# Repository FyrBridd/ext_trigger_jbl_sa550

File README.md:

# WiiM trigger to JBL SA550 serial dongle

A small inline board, powered by a WiiM Ultra's 12 V trigger output, that keeps
a JBL SA550 Classic amplifier switched on and on its STB input over RS232.

**Status (2026-11-11):** board designed and checked, firmware written and
tested against a simulated amp, enclosure designed and checked against the
board and cables. Nothing has been ordered, printed or run on hardware.

## Where to look

| To | Read |
|---|---|
| Review the board before ordering | `docs/hardware-review.md` |
| See the schematic and board | `hardware/fab/schematic.pdf`, `hardware/fab/board.pdf` |
| Check the sums | `docs/hardware-calculations.md` |
| Order from JLCPCB | `docs/hardware-review.md`, section 6 |
| Buy the two cables | `docs/cables.md` |
| Review, order and assemble the enclosure | `docs/enclosure.md`, `enclosure/out/enclosure.pdf` |
| Flash the chip | `docs/flashing.md` |
| Get the first board working | `docs/bring-up.md` |
| Understand the amp's protocol | `docs/research.md` |
| Understand the design decisions | `docs/superpowers/specs/2026-11-10-wiim-trigger-jbl-dongle-design.md` |

## Working on it

All tools (KiCad 10, the AVR compiler, CadQuery, the tests) run in a Docker container.
Run everything through the wrapper `tools/dev`, or use the make targets:

| Command | Does |
|---|---|
| `make hw` | Regenerates the schematic, board and JLCPCB files from `hardware/design/` |
| `make hw-test` | Checks them: KiCad rule checks, schematic against board, files against the circuit |
| `make stock` | Checks every part is in stock at JLCPCB |
| `make fw-test` | Runs the firmware's tests on this machine, against a simulated amp |
| `make fw` | Builds the 16 firmware files in `firmware/release/` |
| `make route` | Re-runs the board autorouter (only after changing the circuit or placement) |
| `make enc` | Regenerates the enclosure's STEP and STL files, pictures and drawing in `enclosure/out/` |
| `make enc-test` | Checks the enclosure fits the board, cables and screws |

The circuit lives in `hardware/design/circuit.py`, the board placement in
`hardware/design/layout.py`, the firmware in `firmware/src/`, the enclosure
in `enclosure/params.py` and `enclosure/model.py`. Files under
`hardware/dongle/`, `hardware/fab/` and `enclosure/out/` are generated; do
not edit them.

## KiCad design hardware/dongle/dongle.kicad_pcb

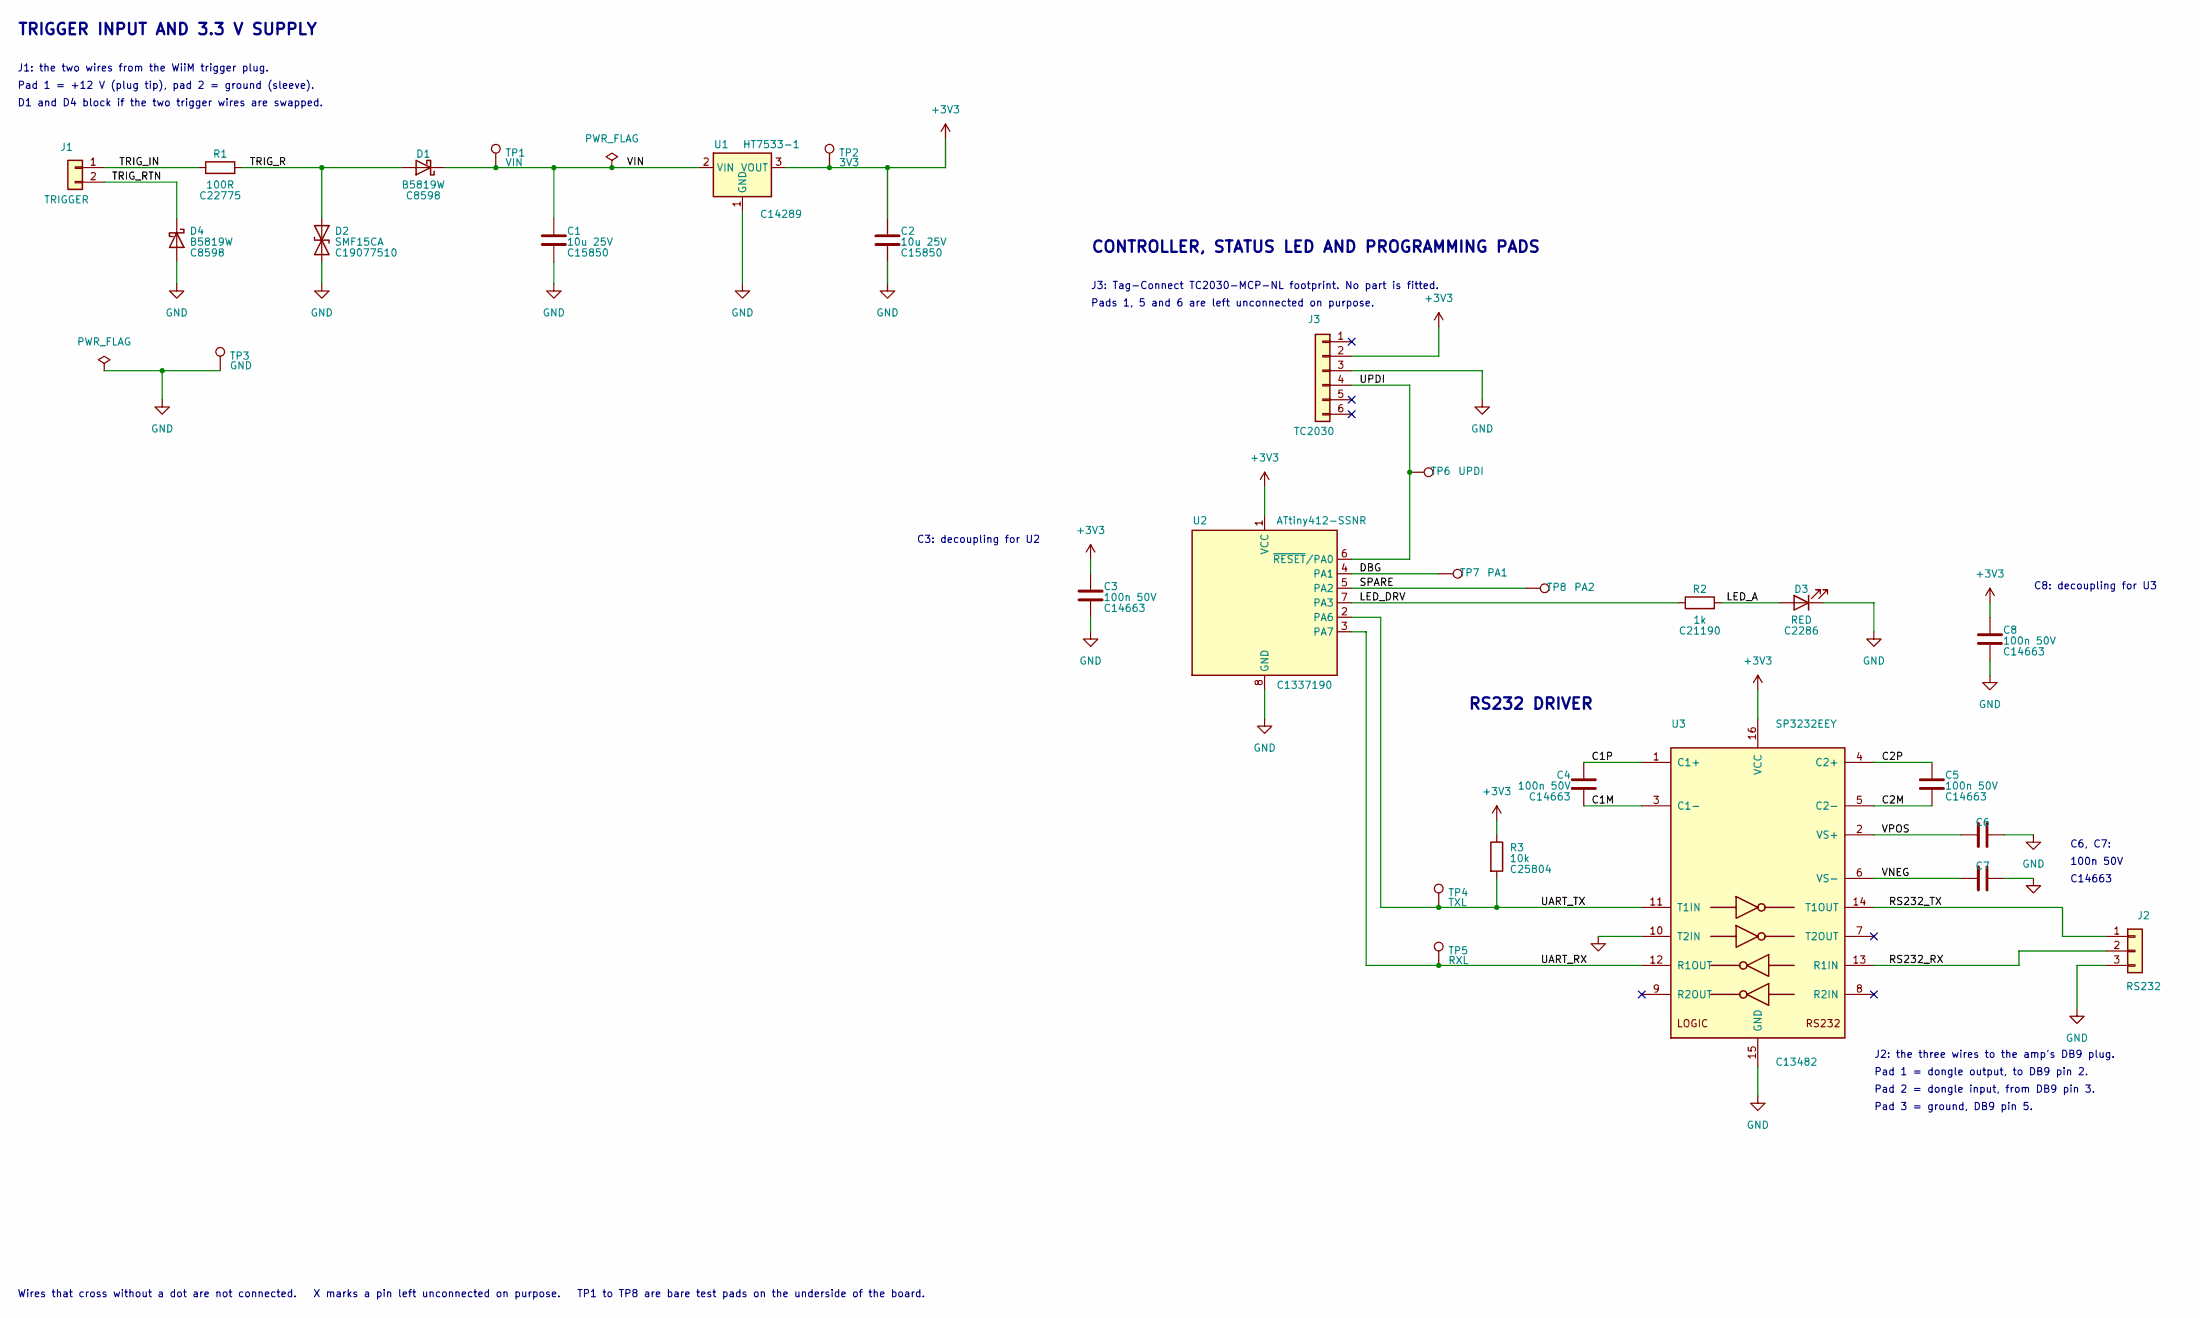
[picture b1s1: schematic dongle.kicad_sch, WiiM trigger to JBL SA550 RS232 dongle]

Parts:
C1, C2: 10u 25V; C_0805_2012Metric; LCSC C15850
C3, C4, C5, C6, C7, C8: 100n 50V; C_0603_1608Metric; LCSC C14663
D1, D4: B5819W; D_SOD-123; LCSC C8598
D2: SMF15CA; D_SOD-123F; LCSC C19077510
D3: RED; LED_0603_1608Metric; LCSC C2286
J1: TRIGGER; WirePads_1x02_Strain
J2: RS232; WirePads_1x03_Strain
J3: TC2030; TC2030-MCP-NL
R1: 100R; R_0603_1608Metric; LCSC C22775
R2: 1k; R_0603_1608Metric; LCSC C21190
R3: 10k; R_0603_1608Metric; LCSC C25804
TP1: VIN; TestPoint_Pad_D1.0mm
TP2: 3V3; TestPoint_Pad_D1.0mm
TP3: GND; TestPoint_Pad_D1.0mm
TP4: TXL; TestPoint_Pad_D1.0mm
TP5: RXL; TestPoint_Pad_D1.0mm
TP6: UPDI; TestPoint_Pad_D1.0mm
TP7: PA1; TestPoint_Pad_D1.0mm
TP8: PA2; TestPoint_Pad_D1.0mm
U1: HT7533-1; SOT-89-3; LCSC C14289
U2: ATtiny412-SSNR; SOIC-8_3.9x4.9mm_P1.27mm; LCSC C1337190
U3: SP3232EEY; TSSOP-16_4.4x5mm_P0.65mm; LCSC C13482

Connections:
+3V3: C2.1, C3.1, C8.1, J3.2, R3.1, TP2.1, U1.3 (VOUT), U2.1 (VCC), U3.16 (VCC)
/C1M: C4.2, U3.3 (C1-)
/C1P: C4.1, U3.1 (C1+)
/C2M: C5.2, U3.5 (C2-)
/C2P: C5.1, U3.4 (C2+)
/DBG: TP7.1, U2.4 (PA1)
/LED_A: D3.2 (A), R2.2
/LED_DRV: R2.1, U2.7 (PA3)
/RS232_RX: J2.2, U3.13 (R1IN)
/RS232_TX: J2.1, U3.14 (T1OUT)
/SPARE: TP8.1, U2.5 (PA2)
/TRIG_IN: J1.1, R1.1
/TRIG_R: D1.2 (A), D2.1 (A1), R1.2
/TRIG_RTN: D4.1 (K), J1.2
/UART_RX: TP5.1, U2.3 (PA7), U3.12 (R1OUT)
/UART_TX: R3.2, TP4.1, U2.2 (PA6), U3.11 (T1IN)
/UPDI: J3.4, TP6.1, U2.6 (~RESET/PA0)
/VIN: C1.1, D1.1 (K), TP1.1, U1.2 (VIN)
/VNEG: C7.2, U3.6 (VS-)
/VPOS: C6.1, U3.2 (VS+)
GND: C1.2, C2.2, C3.2, C6.2, C7.1, C8.2, D2.2 (A2), D3.1 (K), D4.2 (A), J2.3, J3.3, TP3.1, U1.1 (GND), U2.8 (GND), U3.10 (T2IN), U3.15 (GND)

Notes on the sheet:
TRIGGER INPUT AND 3.3 V SUPPLY
J1: the two wires from the WiiM trigger plug.
Pad 1 = +12 V (plug tip), pad 2 = ground (sleeve).
D1 and D4 block if the two trigger wires are swapped.
CONTROLLER, STATUS LED AND PROGRAMMING PADS
J3: Tag-Connect TC2030-MCP-NL footprint. No part is fitted.
Pads 1, 5 and 6 are left unconnected on purpose.
C3: decoupling for U2
RS232 DRIVER
C8: decoupling for U3
C6, C7:
100n 50V
C14663
J2: the three wires to the amp's DB9 plug.
Pad 1 = dongle output, to DB9 pin 2.
Pad 2 = dongle input, from DB9 pin 3.
Pad 3 = ground, DB9 pin 5.
Wires that cross without a dot are not connected. X marks a pin left unconnected on purpose. TP1 to TP8 are bare test pads on the underside of the board.

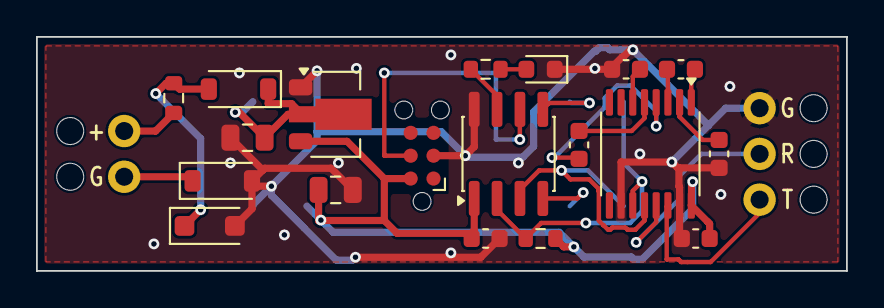
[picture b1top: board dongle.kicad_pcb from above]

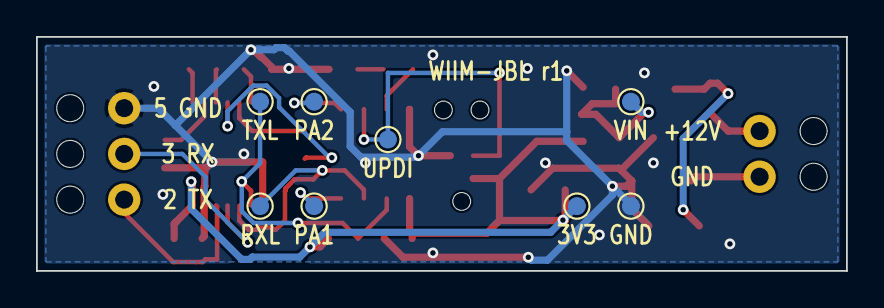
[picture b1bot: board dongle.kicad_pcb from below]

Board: 2 copper layers, 45.0 x 13.0 mm, 29 parts (8 on the bottom side), 21 nets.

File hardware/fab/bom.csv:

Comment,Designator,Footprint,LCSC Part #
HT7533-1,U1,SOT-89-3,C14289
ATtiny412-SSNR,U2,SOIC-8_3.9x4.9mm_P1.27mm,C1337190
SP3232EEY,U3,TSSOP-16_4.4x5mm_P0.65mm,C13482
B5819W,"D1,D4",D_SOD-123,C8598
SMF15CA,D2,D_SOD-123F,C19077510
RED,D3,LED_0603_1608Metric,C2286
10u 25V,"C1,C2",C_0805_2012Metric,C15850
100n 50V,"C3,C4,C5,C6,C7,C8",C_0603_1608Metric,C14663
100R,R1,R_0603_1608Metric,C22775
1k,R2,R_0603_1608Metric,C21190
10k,R3,R_0603_1608Metric,C25804

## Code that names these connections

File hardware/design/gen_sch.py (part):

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    s.place("J1", 14, 30, mirror=True, text={"Reference": (-1.5, -3.6, None), "Value": (-1.5, 5.6, None)})
    r1_in, r1_out = s.two_pin("R1", 24, 30, "1", "right")
    s.wire(P("J1", "1"), r1_in)
    s.label("TRIG_IN", 17, 30)
    d1_a, d1_k = s.two_pin("D1", 38, 30, "2", "right")        # anode in, cathode out
    s.wire(r1_out, d1_a)
    s.label("TRIG_R", 26, 30)
    d2_top, d2_bottom = s.two_pin("D2", 31, 35, "1", "down")  # surge clamp to ground
    s.wire((31, 30), d2_top)
    s.wire(d2_bottom, (31, 38))
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    s.gnd(70, 38)
    d4_k, d4_a = s.two_pin("D4", 21, 35, "1", "down")         # cathode to the return wire
    s.wire(P("J1", "2"), (21, 31), d4_k)
    s.label("TRIG_RTN", 16.5, 31)
    s.wire(d4_a, (21, 38))
    s.gnd(21, 38)
    s.note("D1 and D4 block if the two trigger wires are swapped.", 10, 25.9)
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
    s.place("J3", 100, 44, mirror=True, text={"Reference": (-1.5, -9.0, None), "Value": (-1.5, 10.6, None)})
    s.wire(P("J3", "4"), (106, 45), (106, 57), P("U2", "6"))
    s.label("UPDI", 102.5, 45)
    s.test_pad("TP6", 106, 51, side="right")
    s.wire(P("J3", "2"), (108, 43), (108, 41))
    s.vcc(108, 41)
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    s.gnd(111, 46)

    s.wire(P("U2", "4"), (108, 58))
    s.label("DBG", 102.5, 58)
    s.test_pad("TP7", 108, 58, side="right")
    s.wire(P("U2", "5"), (114, 59))
    s.label("SPARE", 102.5, 59)
    s.test_pad("TP8", 114, 59, side="right")

    r2_in, r2_out = s.two_pin("R2", 126, 60, "1", "right")
    s.wire(P("U2", "7"), r2_in)
    s.label("LED_DRV", 102.5, 60)
    d3_a, d3_k = s.two_pin("D3", 133, 60, "2", "right")       # anode from the resistor
    s.wire(r2_out, d3_a)
    s.label("LED_A", 127.8, 60)
    s.wire(d3_k, (138, 60), (138, 62))
    s.gnd(138, 62)

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
    # logic side: controller to driver
    s.wire(P("U2", "2"), (104, 61), (104, 81), P("U3", "11"))
    s.label("UART_TX", 115, 81)
    s.test_pad("TP4", 108, 81)
    r3_top, r3_bottom = s.two_pin("R3", 112, 77.5, "1", "down")  # holds the line idle while U2 is in reset
    s.wire(r3_top, (112, 75))
    s.vcc(112, 75)
    s.wire(r3_bottom, (112, 81))
    s.wire(P("U2", "3"), (103, 62), (103, 85), P("U3", "12"))
    s.label("UART_RX", 115, 85)
    s.test_pad("TP5", 108, 85)
    s.wire(P("U3", "10"), (119, 83))                             # unused driver input tied off
    s.gnd(119, 83, named=False)
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                       "Value": (118 * G - 2.2, 72.5 * G + 0.3, "right"),
                       "LCSC": (118 * G - 2.2, 72.5 * G + 2.2, "right")}
    s.wire(c4_top, P("U3", "1"))
    s.label("C1P", 118.5, 71)
    s.wire(c4_bottom, P("U3", "3"))
    s.label("C1M", 118.5, 74)
    c5_top, c5_bottom = s.two_pin("C5", 142, 72.5, "1", "down")
    s.wire(P("U3", "4"), c5_top)
    s.label("C2P", 138.5, 71)
    s.wire(P("U3", "5"), c5_bottom)
    s.label("C2M", 138.5, 74)
    c6_in, c6_out = s.two_pin("C6", 145.5, 76, "1", "right")
    s.wire(P("U3", "2"), c6_in)
    s.label("VPOS", 138.5, 76)
    s.wire(c6_out, (149, 76))
    s.gnd(149, 76)
    c7_in, c7_out = s.two_pin("C7", 145.5, 79, "2", "right")
    s.wire(P("U3", "6"), c7_in)
    s.label("VNEG", 138.5, 79)
    s.wire(c7_out, (149, 79))
    s.gnd(149, 79, named=False)
    s.text_at["C6"] = {"Reference": (145.5 * G, 76 * G - 2.2, None)}       # no room for three lines each:
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    # RS232 side: driver to the amp
    s.place("J2", 156, 84, text={"Reference": (1.5, -6.2, None), "Value": (1.5, 6.2, None)})
    s.wire(P("U3", "14"), (151, 81), (151, 83), P("J2", "1"))
    s.label("RS232_TX", 139, 81)
    s.wire(P("U3", "13"), (148, 85), (148, 84), P("J2", "2"))
    s.label("RS232_RX", 139, 85)
    s.wire(P("J2", "3"), (152, 85), (152, 88))
    s.gnd(152, 88)
    s.note("J2: the three wires to the amp's DB9 plug.", 138, 91.5)
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
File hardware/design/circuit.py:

"""The dongle's circuit: parts and nets. This file is the single source of truth.

The schematic and the board are generated from it; tests compare both back to it.
Pin numbers are package pin numbers. See the design document, sections 5 and 6.
"""
from dataclasses import dataclass


@dataclass(frozen=True)
class Part:
    ref: str
    value: str
    symbol: str      # KiCad library symbol, "Library:Name"
    footprint: str   # KiCad footprint, "Library:Name"
    lcsc: str | None  # JLCPCB part number; None for things JLCPCB does not fit
    assemble: bool


R0603 = "Resistor_SMD:R_0603_1608Metric"
C0603 = "Capacitor_SMD:C_0603_1608Metric"
C0805 = "Capacitor_SMD:C_0805_2012Metric"
TESTPAD = "TestPoint:TestPoint_Pad_D1.0mm"

# What each test pad is for; also its silkscreen label.
TEST_PADS = {
    "TP1": "VIN", "TP2": "3V3", "TP3": "GND", "TP4": "TXL",
    "TP5": "RXL", "TP6": "UPDI", "TP7": "PA1", "TP8": "PA2",
}

_parts = [
    Part("U1", "HT7533-1", "Regulator_Linear:HT75xx-1-SOT89", "Package_TO_SOT_SMD:SOT-89-3", "C14289", True),
    Part("U2", "ATtiny412-SSNR", "MCU_Microchip_ATtiny:ATtiny412-SS", "Package_SO:SOIC-8_3.9x4.9mm_P1.27mm", "C1337190", True),
    Part("U3", "SP3232EEY", "Interface_UART:MAX3232", "Package_SO:TSSOP-16_4.4x5mm_P0.65mm", "C13482", True),
    Part("D1", "B5819W", "Device:D_Schottky", "Diode_SMD:D_SOD-123", "C8598", True),
    Part("D2", "SMF15CA", "Device:D_TVS", "Diode_SMD:D_SOD-123F", "C19077510", True),
    Part("D3", "RED", "Device:LED", "LED_SMD:LED_0603_1608Metric", "C2286", True),
    Part("D4", "B5819W", "Device:D_Schottky", "Diode_SMD:D_SOD-123", "C8598", True),
    Part("C1", "10u 25V", "Device:C", C0805, "C15850", True),
    Part("C2", "10u 25V", "Device:C", C0805, "C15850", True),
    *[Part(f"C{i}", "100n 50V", "Device:C", C0603, "C14663", True) for i in range(3, 9)],
    Part("R1", "100R", "Device:R", R0603, "C22775", True),
    Part("R2", "1k", "Device:R", R0603, "C21190", True),
    Part("R3", "10k", "Device:R", R0603, "C25804", True),
    Part("J1", "TRIGGER", "Connector_Generic:Conn_01x02", "dongle:WirePads_1x02_Strain", None, False),
    Part("J2", "RS232", "Connector_Generic:Conn_01x03", "dongle:WirePads_1x03_Strain", None, False),
    Part("J3", "TC2030", "Connector_Generic:Conn_01x06", "dongle:TC2030-MCP-NL", None, False),
    *[Part(ref, label, "Connector:TestPoint", TESTPAD, None, False) for ref, label in TEST_PADS.items()],
]
PARTS: dict[str, Part] = {p.ref: p for p in _parts}

NETS: dict[str, list[tuple[str, str]]] = {
    # Trigger input and 3.3 V supply
    # Each trigger wire meets the circuit only through a diode (D1 in the supply
    # leg, D4 in the return leg), so swapped wires have no path to anything. In
    # particular the return wire is not tied straight to ground: ground is shared
    # with the amp and, through the audio cable, with the WiiM, and a swapped
    # +12 V wire on it would short the WiiM's trigger output.
    "TRIG_IN": [("J1", "1"), ("R1", "1")],
    "TRIG_RTN": [("J1", "2"), ("D4", "1")],                        # D4.1 is the cathode
    "TRIG_R": [("R1", "2"), ("D2", "1"), ("D1", "2")],            # D1.2 is the anode
    "VIN": [("D1", "1"), ("C1", "1"), ("U1", "2"), ("TP1", "1")],  # D1.1 is the cathode
    "+3V3": [("U1", "3"), ("C2", "1"), ("C3", "1"), ("U2", "1"), ("U3", "16"),
             ("C8", "1"), ("R3", "1"), ("J3", "2"), ("TP2", "1")],
    "GND": [("D4", "2"), ("D2", "2"), ("C1", "2"), ("U1", "1"), ("C2", "2"), ("C3", "2"),
            ("U2", "8"), ("U3", "15"), ("U3", "10"), ("C8", "2"), ("C6", "2"), ("C7", "1"),
            ("D3", "1"), ("J2", "3"), ("J3", "3"), ("TP3", "1")],  # D3.1 is the cathode
    # Controller to serial driver (logic level)
    "UART_TX": [("U2", "2"), ("U3", "11"), ("R3", "2"), ("TP4", "1")],
    "UART_RX": [("U2", "3"), ("U3", "12"), ("TP5", "1")],
    # RS232 side, to the amplifier
    "RS232_TX": [("U3", "14"), ("J2", "1")],
    "RS232_RX": [("U3", "13"), ("J2", "2")],
    # Programming, debug and spare
    "UPDI": [("U2", "6"), ("J3", "4"), ("TP6", "1")],
    "DBG": [("U2", "4"), ("TP7", "1")],
    "SPARE": [("U2", "5"), ("TP8", "1")],
    # Status LED
    "LED_DRV": [("U2", "7"), ("R2", "1")],
    "LED_A": [("R2", "2"), ("D3", "2")],                           # D3.2 is the anode
    # Serial driver charge pump
    "C1P": [("U3", "1"), ("C4", "1")],
    "C1M": [("U3", "3"), ("C4", "2")],
    "C2P": [("U3", "4"), ("C5", "1")],
    "C2M": [("U3", "5"), ("C5", "2")],
    "VPOS": [("U3", "2"), ("C6", "1")],
    "VNEG": [("U3", "6"), ("C7", "2")],
}

# Pins deliberately left unconnected.
NO_CONNECT: list[tuple[str, str]] = [
    ("U3", "7"), ("U3", "8"), ("U3", "9"),   # unused second RS232 channel
    ("J3", "1"), ("J3", "5"), ("J3", "6"),   # programming cable MCLR/VPP, PGC, AUX
]

# Datasheet function of every IC pin, for review against the datasheets.
PIN_FUNCTIONS: dict[tuple[str, str], str] = {
    ("U1", "1"): "GND", ("U1", "2"): "VIN", ("U1", "3"): "VOUT",
    ("U2", "1"): "VDD", ("U2", "2"): "PA6/TXD", ("U2", "3"): "PA7/RXD", ("U2", "4"): "PA1",
    ("U2", "5"): "PA2", ("U2", "6"): "PA0/UPDI", ("U2", "7"): "PA3", ("U2", "8"): "GND",
    ("U3", "1"): "C1+", ("U3", "2"): "V+", ("U3", "3"): "C1-", ("U3", "4"): "C2+",
    ("U3", "5"): "C2-", ("U3", "6"): "V-", ("U3", "7"): "T2OUT", ("U3", "8"): "R2IN",
    ("U3", "9"): "R2OUT", ("U3", "10"): "T2IN", ("U3", "11"): "T1IN", ("U3", "12"): "R1OUT",
    ("U3", "13"): "R1IN", ("U3", "14"): "T1OUT", ("U3", "15"): "GND", ("U3", "16"): "VCC",
}
